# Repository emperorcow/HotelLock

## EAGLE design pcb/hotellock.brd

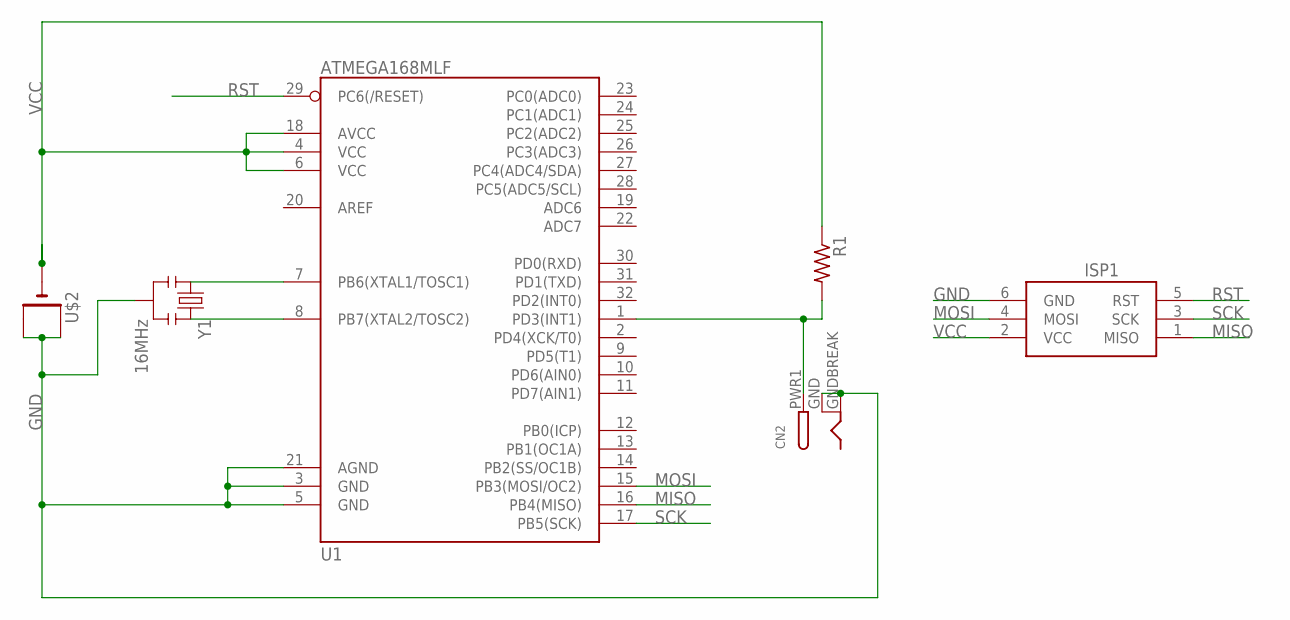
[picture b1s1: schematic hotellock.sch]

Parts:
CN2: DCBARRELSMT; DCJACK_2MM_SMT
ISP1: AVRISP-6; AVRISP
R1: R-US_R0805; R0805
U1: ATMEGA168MLF; MLF32
U$2: CR1220SMT; CR1220-SMD
Y1: 16MHz; RESONATOR-SMD

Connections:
GND: CN2.GND (GNDBREAK), CN2.GNDBREAK (GND), ISP1.6 (GND), U1.3 (GND), U1.21 (AGND), U$2.+$1 (+), U$2.+$2 (+1), Y1.2
MISO: ISP1.1 (MISO), U1.16 (PB4(MISO))
MOSI: ISP1.4 (MOSI), U1.15 (PB3(MOSI/OC2))
unnamed: U1.8 (PB7(XTAL2/TOSC2)), Y1.3
unnamed: U1.7 (PB6(XTAL1/TOSC1)), Y1.1
unnamed: CN2.PWR1 (PWR), R1.2, U1.1 (PD3(INT1))
RST: ISP1.5 (RST), U1.29 (PC6(/RESET))
SCK: ISP1.3 (SCK), U1.17 (PB5(SCK))
VCC: ISP1.2 (VCC), R1.1, U1.6 (VCC), U1.18 (AVCC), U$2.-

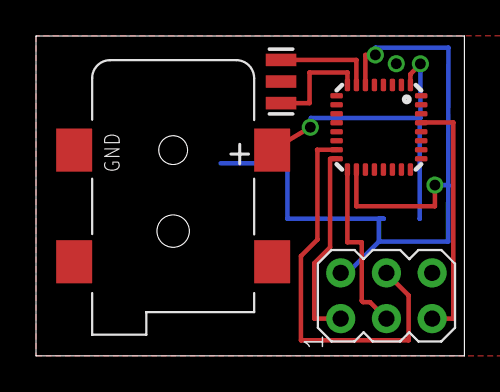
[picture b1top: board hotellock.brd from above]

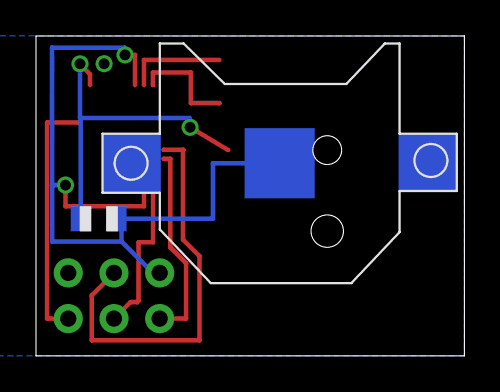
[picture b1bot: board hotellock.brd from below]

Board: 2 copper layers, 23.8 x 17.8 mm, 6 parts (2 on the bottom side), 9 nets.

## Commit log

2014-04-14 Initial Design

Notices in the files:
parts and their libraries:
SparkFun-DigitalIC: Licensing: Creative Commons ShareAlike 4.0 International - https://creativecommons.org/licenses/by-sa/4.0
